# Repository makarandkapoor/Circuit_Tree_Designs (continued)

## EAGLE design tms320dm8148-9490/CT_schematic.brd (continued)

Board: 2 copper layers, 379 parts (0 on the bottom side), 196 nets, no tracks yet.

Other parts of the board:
J1: PJ-037B; PJ-037B_PACKAGE
U1: tms320dm8148SCYE2; BFBGA-684
U2: MD-40S
U3: AT25320B-SSHL-T; SOIC-8
U4: DP83867CSRGZT; VFQFPN48
U5: 7499511611A
U6: LAN8710AI-EZK; QFN-32
U7: 7498011122R
U8: 24AA1025T-I/SN; SOIC-8
U9: WM8731CLSEFL; QFN-28
U10, U11: SJ-43515TS-SMT-TR
U12, U13: ABLS-20.000MHZ-B4-T
U14: ABLS-25.000MHZ-B2F-T
U15: ASFL1-12.288MHZ-EC-T; ASFL1
U16: tps54525PWP; HTSSOP14
U17, U23: LP2951ACSDX/NOPB; WSON-8
U18, U19, U20: LTC3601EUD#PBF; QFN-16_EP
U21, U22: LP3878SDX-ADJ/NOPB; WSON-8
U24: LTC2928CUHF#PBF; QFN-38_UHF
U25, U26, U27, U28: IRF8306MTRPbF; IRF8306MTRPBF
U29: 4-1437565-2; SW_4-1437565-2
U30: Q65110A2395; LGM67K-G1J2-24-Z
U31, U32, U33: nc7sz125m5x; NC7SZ125M5X

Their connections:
CLK_CRYSTAL_U1_AH2: U1.AH2, U12.1; also elsewhere on the board
CLK_CRYSTAL_U1_AH3: U1.AH3, U12.2; also elsewhere on the board
CLK_CRYSTAL_U1_R1: U1.R1, U13.1; also elsewhere on the board
CLK_CRYSTAL_U1_T1: U1.T1, U13.2; also elsewhere on the board
CLK_CRYSTAL_U4_14: U4.14, U14.2; also elsewhere on the board
CLK_CRYSTAL_U4_15: U4.15, U14.1; also elsewhere on the board
CLK_U9_1: U9.1, U15.3
NET_U1_AA15: U1.AA15, U1.AA17, U1.AB14, U1.AB16, U1.M8, U1.N7, U1.P8, U1.T7, U1.U21, U1.U22, U1.V20, U1.Y11, U1.Y16
NET_U1_AA27: U1.AA27; also elsewhere on the board
NET_U1_AA28: U1.AA28; also elsewhere on the board
NET_U1_AB6: U1.AB6, U8.5; also elsewhere on the board
NET_U1_AB27: U1.AB27; also elsewhere on the board
NET_U1_AB28: U1.AB28; also elsewhere on the board
NET_U1_AC4: U1.AC4, U8.6; also elsewhere on the board
NET_U1_AG22: U1.AG22; also elsewhere on the board
NET_U1_AG23: U1.AG23; also elsewhere on the board
NET_U1_AH23: U1.AH23; also elsewhere on the board
NET_U1_B1: U1.B1; also elsewhere on the board
NET_U1_B27: U1.B27; also elsewhere on the board
NET_U1_G14: U1.G14; also elsewhere on the board
NET_U1_G15: U1.G15; also elsewhere on the board
NET_U1_H28: U1.H28, U4.16, U6.17; also elsewhere on the board
NET_U1_J5: U1.J5, U33.4; also elsewhere on the board
NET_U1_K12: U1.K9, U1.K12, U1.K18, U1.L15, U1.L17, U1.L19, U1.M16, U1.M18, U1.N17, U1.N19, U1.P12, U1.P14, U1.P16, U1.R15, U1.R17, U1.R19, U1.T12, U1.U11, U1.U13, U1.U17, U1.U19, U1.W11
NET_U1_L18: U1.L18; also elsewhere on the board
NET_U1_M11: U1.M11; also elsewhere on the board
NET_U1_N10: U1.N10; also elsewhere on the board
NET_U1_N11: U1.N11; also elsewhere on the board
NET_U1_P10: U1.P10; also elsewhere on the board
NET_U1_P18: U1.P18; also elsewhere on the board
NET_U1_P24: U1.P24, U4.17, U6.16; also elsewhere on the board
NET_U1_R11: U1.R11; also elsewhere on the board
NET_U1_T10: U1.T10; also elsewhere on the board
NET_U1_T11: U1.T11; also elsewhere on the board
NET_U1_U10: U1.U9, U1.U10
NET_U1_U23: U1.U23; also elsewhere on the board
NET_U1_U24: U1.U24; also elsewhere on the board
NET_U1_U25: U1.U25; also elsewhere on the board
NET_U1_U26: U1.U26; also elsewhere on the board
NET_U1_V14: U1.V14; also elsewhere on the board
NET_U1_V24: U1.V24; also elsewhere on the board
NET_U1_V25: U1.V25; also elsewhere on the board
NET_U1_V26: U1.V26; also elsewhere on the board
NET_U1_V27: U1.V27; also elsewhere on the board
NET_U1_W10: U1.W9, U1.W10
NET_U1_W14: U1.W14; also elsewhere on the board
NET_U1_W19: U1.W19, U1.W20
NET_U1_W27: U1.W27; also elsewhere on the board
NET_U1_Y25: U1.Y25; also elsewhere on the board
NET_U1_Y26: U1.Y26; also elsewhere on the board
NET_U1_Y27: U1.Y27; also elsewhere on the board
NET_U1_Y28: U1.Y28; also elsewhere on the board
NET_U2_3: U1.AH24, U2.3; also elsewhere on the board
NET_U2_4: U1.AH22, U2.4; also elsewhere on the board
NET_U3_3: U3.3; also elsewhere on the board
NET_U3_7: U3.7; also elsewhere on the board
NET_U4_12: U4.12; also elsewhere on the board
NET_U4_18: U4.18; also elsewhere on the board
NET_U4_20: U4.20; also elsewhere on the board
NET_U4_40: U4.40; also elsewhere on the board
NET_U4_43: U4.43, U31.4; also elsewhere on the board
NET_U4_44: U4.44; also elsewhere on the board
NET_U4_45: U4.45; also elsewhere on the board
NET_U4_46: U4.46; also elsewhere on the board
NET_U5_2: U4.8, U5.2
NET_U5_3: U4.7, U5.3
NET_U5_4: U4.4, U5.4
NET_U5_5: U4.5, U5.5
NET_U5_6: U5.1, U5.6, U5.7, U5.12; also elsewhere on the board
NET_U5_8: U4.10, U5.8
NET_U5_9: U4.11, U5.9
NET_U5_10: U4.2, U5.10
NET_U5_11: U4.1, U5.11
NET_U5_18: U5.18; also elsewhere on the board
NET_U5_19: U5.19; also elsewhere on the board
NET_U6_1: U6.1, U6.27; also elsewhere on the board
NET_U6_6: U6.6; also elsewhere on the board
NET_U6_7: U6.7; also elsewhere on the board
NET_U6_8: U6.8; also elsewhere on the board
NET_U6_9: U6.9; also elsewhere on the board
NET_U6_18: U6.18; also elsewhere on the board
NET_U6_19: U6.19, U32.4; also elsewhere on the board
NET_U6_32: U6.32; also elsewhere on the board
NET_U7_1: U6.29, U7.1; also elsewhere on the board
NET_U7_3: U6.28, U7.3; also elsewhere on the board
NET_U7_4: U6.31, U7.4; also elsewhere on the board
NET_U7_5: U7.2, U7.5; also elsewhere on the board
NET_U7_6: U6.30, U7.6; also elsewhere on the board
NET_U7_8: U7.8; also elsewhere on the board
NET_U7_9: U7.9; also elsewhere on the board
NET_U7_11: U6.2, U7.11
NET_U7_12: U7.12; also elsewhere on the board
NET_U7_13: U7.13, U7.14; also elsewhere on the board
NET_U8_1: U8.1; also elsewhere on the board
NET_U8_2: U8.2; also elsewhere on the board
NET_U8_3: U8.3; also elsewhere on the board
NET_U9_20: U9.20; also elsewhere on the board
NET_U10_2: U10.2; also elsewhere on the board
NET_U10_5: U10.5; also elsewhere on the board
NET_U11_5: U11.5; also elsewhere on the board
NET_U16_2: U16.2; also elsewhere on the board
NET_U16_3: U16.3; also elsewhere on the board
NET_U16_4: U16.4; also elsewhere on the board
NET_U16_10: U16.10, U16.11; also elsewhere on the board
NET_U16_12: U16.12; also elsewhere on the board
NET_U17_5: U17.5; also elsewhere on the board
NET_U17_7: U17.7; also elsewhere on the board
NET_U18_3: U18.3, U18.4; also elsewhere on the board
NET_U18_6: U18.6; also elsewhere on the board
NET_U18_7: U18.7, U18.12; also elsewhere on the board
NET_U18_10: U18.10; also elsewhere on the board
NET_U18_11: U18.11; also elsewhere on the board
NET_U19_3: U19.3, U19.4; also elsewhere on the board
NET_U19_6: U19.6; also elsewhere on the board
NET_U19_7: U19.7, U19.12; also elsewhere on the board
NET_U19_10: U19.10; also elsewhere on the board
NET_U19_11: U19.11; also elsewhere on the board
NET_U20_3: U20.3, U20.4; also elsewhere on the board
NET_U20_6: U20.6; also elsewhere on the board
NET_U20_7: U20.7, U20.12; also elsewhere on the board
NET_U20_10: U20.10; also elsewhere on the board
NET_U20_11: U20.11; also elsewhere on the board
NET_U21_1: U21.1; also elsewhere on the board
NET_U21_6: U21.6; also elsewhere on the board
NET_U21_8: U21.8; also elsewhere on the board
NET_U22_1: U22.1; also elsewhere on the board
NET_U22_6: U22.6; also elsewhere on the board
NET_U22_8: U22.8; also elsewhere on the board
NET_U23_5: U23.5; also elsewhere on the board
NET_U23_7: U23.7; also elsewhere on the board
NET_U24_3: U24.3; also elsewhere on the board
NET_U24_6: U24.6; also elsewhere on the board
NET_U24_7: U24.7; also elsewhere on the board
NET_U24_8: U24.8; also elsewhere on the board
NET_U24_9: U24.9; also elsewhere on the board
NET_U24_16: U24.16; also elsewhere on the board
NET_U24_18: U24.18; also elsewhere on the board
NET_U24_19: U24.19, U24.20; also elsewhere on the board
NET_U24_21: U24.21, U31.2, U32.2, U33.2; also elsewhere on the board
NET_U24_22: U24.11, U24.22; also elsewhere on the board
NET_U24_26: U24.26; also elsewhere on the board
NET_U24_27: U24.27; also elsewhere on the board
NET_U24_28: U24.28; also elsewhere on the board
NET_U24_30: U24.30; also elsewhere on the board
NET_U24_32: U24.32; also elsewhere on the board
NET_U24_38: U24.38; also elsewhere on the board
NET_U25_3: U24.2, U25.3
NET_U26_3: U24.37, U26.3
NET_U27_3: U24.31, U27.3
NET_U28_3: U24.29, U28.3
NET_U29_1: U29.1, U29.2
NET_U29_3: U29.3, U29.4
PROC_EMAC0_RGRXC: U1.L24, U4.32
PROC_EMAC0_RGRXCTL: U1.L23, U4.38; also elsewhere on the board
PROC_EMAC0_RGRXD0: U1.P23, U4.33; also elsewhere on the board
PROC_EMAC0_RGRXD1: U1.R23, U4.34; also elsewhere on the board
PROC_EMAC0_RGRXD2: U1.R25, U4.35
PROC_EMAC0_RGRXD3: U1.T23, U4.36
PROC_EMAC0_RGTXC: U1.H27, U4.29
PROC_EMAC0_RGTXCTL: U1.J26, U4.37
PROC_EMAC0_RGTXD0: U1.G28, U4.28
PROC_EMAC0_RGTXD1: U1.G27, U4.27
PROC_EMAC0_RGTXD2: U1.F28, U4.26
PROC_EMAC0_RGTXD3: U1.H26, U4.25
PROC_EMAC1_RMCRSDV: U1.AC17, U6.15; also elsewhere on the board
PROC_EMAC1_RMRXD0: U1.H22, U6.11; also elsewhere on the board
PROC_EMAC1_RMRXD1: U1.AF20, U6.10; also elsewhere on the board
PROC_EMAC1_RMRXER: U1.AB21, U6.13; also elsewhere on the board
PROC_EMAC1_RMTXD0: U1.AE18, U6.22
PROC_EMAC1_RMTXD1: U1.AC21, U6.23
PROC_EMAC1_RMTXEN: U1.AC16, U6.21
PROC_MCA0_ACLKX: U1.R4, U9.7
PROC_MCA0_AFSX: U1.L3, U9.9, U9.11
PROC_MCA0_AXR7: U1.L2, U9.10
PROC_MCA0_AXR8: U1.L1, U9.8
PROC_SPI0_D0: U1.AE3, U3.5
PROC_SPI0_D1: U1.AF3, U3.2
PROC_SPI0_SCLK: U1.AC7, U3.6
PROC_SPI0_SCS0: U1.AD6, U3.1; also elsewhere on the board
VCC_13V3: J1.1, U24.23, U25.1, U25.2, U25.6, U25.7, U26.1, U26.2, U26.6, U26.7, U27.1, U27.2, U27.6, U27.7, U28.1, U28.2, U28.6, U28.7; also elsewhere on the board
VCC_S1_13V3: U16.7, U16.13, U16.14, U17.8, U25.4, U25.5; also elsewhere on the board
VCC_S2_13V3: U18.15, U18.16, U26.4, U26.5; also elsewhere on the board
VCC_S3_13V3: U19.15, U19.16, U20.15, U20.16, U21.4, U22.4, U27.4, U27.5; also elsewhere on the board
VCC_S4_13V3: U23.8, U28.4, U28.5; also elsewhere on the board
VCC_TIER1_1V35: U1.K9, U1.K10, U1.L9, U1.L10, U1.L11, U1.L12, U1.L14, U1.L15, U1.M10, U1.M12, U1.M13, U1.M14, U1.N9, U1.N13, U1.N14, U1.T14, U1.T15, U1.T16, U1.U15, U1.U16, U1.V15, U1.V16, U16.1; also elsewhere on the board
VCC_TIER1_3V3: U15.4, U17.1, U31.5, U32.5, U33.5; also elsewhere on the board
VCC_TIER3_2V5: U4.3, U4.9, U21.5; also elsewhere on the board
VCC_TIER3_3V3: U22.5; also elsewhere on the board
VCC_TIER4_3V3: U1.AA13, U23.1; also elsewhere on the board

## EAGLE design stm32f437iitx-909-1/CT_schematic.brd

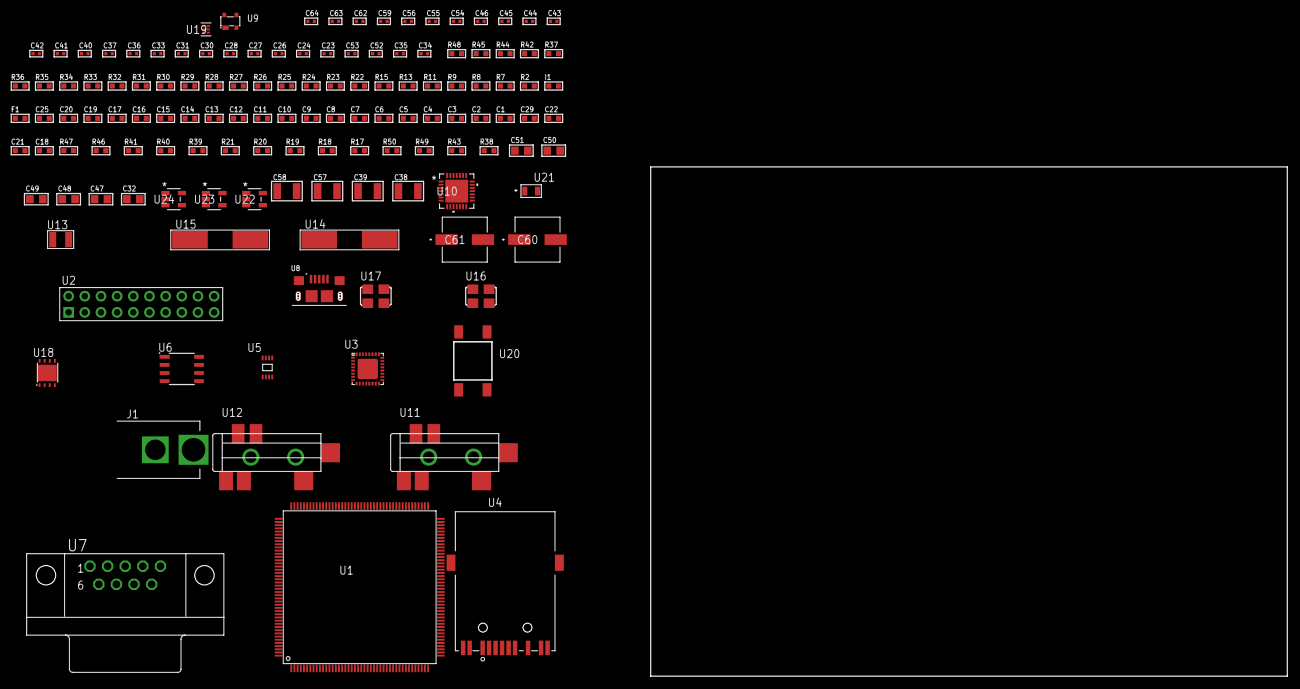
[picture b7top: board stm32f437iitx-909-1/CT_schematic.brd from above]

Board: 2 copper layers, 132 parts (0 on the bottom side), 80 nets, no tracks yet.

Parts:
C1, C20, C25: 1e-06; C0603
C2, C3, C4, C5, C6, C7, C8, C9, C10, C11, C12, C13, C14, C15, C16, C17: 1e-07; C0603
C18: 4.7e-06; C0603
C19: 1e-08; C0603
C21, C22, C29: 2.2e-06; C0603
C23, C24: 1e-11; C0402
C26, C27, C28, C30, C31, C33, C37, C42, C43, C44, C45, C46, C59: 1e-07; C0402
C32, C47, C48, C49, C50, C51: 1e-05; C0805
C34, C35, C52, C53: 2.2e-11; C0402
C36, C54, C55, C56, C62, C63, C64: 1e-08; C0402
C38, C39: 2.2e-05; C1210
C40, C41: 1e-09; C0402
C57, C58: 1e-05; C1210
C60, C61: 0.0001; EXV-9H
F1: 240.0; L0603
I1: 97.0; R0603
J1: PJ-037B; PJ-037B_PACKAGE
R2, R31, R33, R34, R35, R45: 1000.0; R0603
R7, R8, R27, R28, R29, R30, R32, R36: 4700.0; R0603
R9, R11, R13, R15: 2200.0; R0603
R17, R18, R19, R20, R21, R46, R47: 10000.0; R0603
R22, R23: 0.1; R0603
R24: 200.0; R0603
R25: 220.0; R0603
R26: 6490.0; R0603
R37: 120.0; R0603
R38: 470000.0; R0603
R39, R40, R41: 47000.0; R0603
R42: 680.0; R0603
R43: 100000.0; R0603
R44: 2231.0; R0603
R48: 9100.0; R0603
R49: 680000.0; R0603
R50: 120000.0; R0603
U1: STM32F437IIT6; LQFP176
U2: TST-110-05-T-D-RA
U3: KSZ8081RNBIA-TR; QFN-32
U4: 7498011122R
U5: 24AA08T-I/MNY; TDFN-8/6MM
U6: SN65HVD230D; SOIC-8
U7: 182-009-113R531; 182-009-MALE
U8: 10118193-0001LF; FCI_10118193-0001LF
U9: prtr5v0u2ax; SOT143B
U10: WM8731CLSEFL; QFN-28
U11, U12: SJ-43515TS-SMT-TR
U13: ABS07-32.768KHZ-7-T
U14: ABLS-25.000MHZ-B2F-T
U15: ABLS-12.288MHZ-B4-T
U16: ASFL1-25MHZ-NCS; ASFL1
U17: ASFL1-50MHZ-NCS; ASFL1
U18: LP3878SDX-ADJ/NOPB; WSON-8
U19: TPS3895ADRYR; SON-6
U20: 4-1437565-2; SW_4-1437565-2
U21: Q65110A2395; LGM67K-G1J2-24-Z
U22, U23, U24: nc7sz125m5x; NC7SZ125M5X

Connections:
CLK_CRYSTAL_U1_9: C23.1, U1.9, U13.1
CLK_CRYSTAL_U1_10: C24.1, U1.10, U13.2
CLK_CRYSTAL_U3_8: C34.1, U3.8, U14.2
CLK_CRYSTAL_U3_9: C35.1, U3.9, U14.1
CLK_CRYSTAL_U10_1: C52.1, U10.1, U15.1
CLK_CRYSTAL_U10_2: C53.1, U10.2, U15.2
CLK_U1_29: U1.29, U16.3
CLK_U1_41: U1.41, U17.3
GND: C1.2, C2.2, C3.2, C4.2, C5.2, C6.2, C7.2, C8.2, C9.2, C10.2, C11.2, C12.2, C13.2, C14.2, C15.2, C16.2, C17.2, C18.2, C19.2, C20.2, C21.2, C22.2, C23.2, C24.2, C25.2, C26.2, C27.2, C28.2, C29.2, C30.2, C31.2, C32.2, C33.2, C34.2, C35.2, C36.2, C37.2, C41.2, C42.2, C43.2, C44.2, C45.2, C46.2, C47.2, C48.2, C49.2, C50.2, C51.2, C52.2, C53.2, C54.2, C55.2, C56.2, C57.2, C58.2, C59.2, C60.2, C61.2, C62.2, C63.2, C64.2, J1.2, R2.2, R20.2, R22.2, R23.2, R26.2, R28.2, R31.2, R33.2, R34.2, R35.2, R38.2, R39.2, R40.2, R41.2, R45.2, R48.2, R50.2, U1.14, U1.22, U1.37, U1.61, U1.71, U1.90, U1.102, U1.113, U1.122, U1.126, U1.135, U1.148, U1.158, U2.4, U2.6, U2.8, U2.10, U2.12, U2.14, U2.16, U2.18, U2.20, U3.1, U3.EXP, U4.1, U4.10, U5.4, U5.7, U6.2, U7.5, U8.5, U8.6, U8.7, U8.8, U8.9, U9.1, U10.4, U10.15, U10.19, U10.25, U10.26, U10.29, U11.1, U12.1, U16.2, U17.2, U18.3, U18.PAD, U19.2, U21.C, U22.2, U22.3, U23.1, U23.3, U24.1, U24.3
NET_U1_31: R8.1, U1.31, U24.4
NET_U1_33: R13.1, U1.33, U3.12
NET_U1_39: C19.1, C20.1, F1.1, U1.38, U1.39
NET_U1_42: R15.1, U1.42, U3.11
NET_U1_48: R20.1, U1.48
NET_U1_58: R19.1, U1.58
NET_U1_81: C21.1, U1.81
NET_U1_125: C22.1, U1.125
NET_U1_164: R9.1, U1.164, U5.6
NET_U1_165: R11.1, U1.165, U5.5
NET_U1_166: R18.1, U1.166
NET_U1_171: R17.1, U1.171
NET_U1_176: U20.3, U20.4
NET_U3_2: C29.1, C30.1, U3.2
NET_U3_3: C31.1, I1.1, U3.3
NET_U3_10: R26.1, U3.10
NET_U3_13: R29.1, U3.13
NET_U3_14: R30.1, U3.14
NET_U3_19: R28.1, U3.19
NET_U3_20: R34.1, U3.20
NET_U3_21: R27.1, U3.21
NET_U3_28: R32.1, U3.28
NET_U3_29: R33.1, U3.29
NET_U3_31: R35.1, U3.31
NET_U3_32: R7.1, U3.32, U23.4
NET_U4_1: U3.7, U4.1
NET_U4_2: C27.1, U4.2
NET_U4_3: U3.6, U4.3
NET_U4_4: U3.5, U4.4
NET_U4_5: C28.1, U4.5
NET_U4_6: U3.4, U4.6
NET_U4_8: R23.1, U4.8
NET_U4_9: R24.1, U4.9
NET_U4_12: R25.1, U4.12
NET_U4_13: R22.1, U4.13, U4.14
NET_U6_6: R37.2, U6.6
NET_U6_8: R38.1, U6.8
NET_U7_2: R37.2, U6.6, U7.2
NET_U7_3: R37.1, U6.7, U7.3
NET_U10_20: C46.1, C51.1, U10.20
NET_U11_2: C39.1, R40.1, U11.2
NET_U11_5: C38.1, R39.1, U11.5
NET_U12_5: C40.1, C41.1, R41.1, R42.1, U12.5
NET_U18_1: C56.1, U18.1
NET_U18_6: R44.2, R45.1, U18.6
NET_U18_8: R43.1, U18.8
NET_U19_1: R47.1, R48.1, U19.1
NET_U19_3: R49.2, R50.1, U19.3
NET_U19_4: R46.1, U19.4, U22.4, U23.2, U24.2
NET_U20_1: R2.1, U20.1, U20.2
PROC_CAN1_RX: U1.11, U6.4
PROC_CAN1_TX: U1.128, U6.1
PROC_ETH_CRS_DV: U1.53, U3.18
PROC_ETH_RXD0: R36.1, U1.54, U3.16
PROC_ETH_RXD1: R31.1, U1.55, U3.15
PROC_ETH_TXD0: U1.92, U3.24
PROC_ETH_TXD1: U1.93, U3.25
PROC_ETH_TX_EN: U1.80, U3.23
PROC_I2S2_CK: U1.79, U10.7
PROC_I2S2_EXT_SD: U1.34, U10.10
PROC_I2S2_SD: U1.35, U10.8
PROC_I2S2_WS: U1.131, U10.9, U10.11
PROC_SYS_JTCK_SWCLK: U1.137, U2.9
PROC_SYS_JTDO_SWO: U1.161, U2.13
PROC_SYS_JTMS_SWDIO: U1.124, U2.7
PROC_USB_OTG_FS_DM: U1.122, U8.2, U9.3
PROC_USB_OTG_FS_DP: U1.123, U8.3, U9.2
PROC_USB_OTG_FS_VBUS: C25.1, U1.120, U8.1, U9.4
RST_OUT_U2_SRESET_B: R21.1, U2.15, U22.1
VCC_S1_12V1: C57.1, C60.1, C61.1, J1.1, R43.2, U18.4
VCC_TIER1_3V3: C1.1, C2.1, C3.1, C4.1, C5.1, C6.1, C7.1, C8.1, C9.1, C10.1, C11.1, C12.1, C13.1, C14.1, C15.1, C16.1, C17.1, C18.1, C26.1, C32.1, C33.1, C36.1, C37.1, C42.1, C43.1, C44.1, C45.1, C47.1, C48.1, C49.1, C50.1, C54.1, C55.1, C58.1, C59.1, C62.1, C63.1, C64.1, F1.2, I1.2, R7.2, R8.2, R9.2, R11.2, R13.2, R15.2, R17.2, R18.2, R19.2, R21.2, R27.2, R29.2, R30.2, R32.2, R36.2, R44.1, R46.2, R47.2, R49.1, U1.6, U1.15, U1.23, U1.36, U1.49, U1.62, U1.72, U1.82, U1.91, U1.103, U1.114, U1.127, U1.136, U1.149, U1.159, U1.172, U2.1, U3.17, U5.8, U6.3, U10.3, U10.5, U10.12, U10.18, U16.4, U17.4, U18.5, U19.6, U22.5, U23.5, U24.5

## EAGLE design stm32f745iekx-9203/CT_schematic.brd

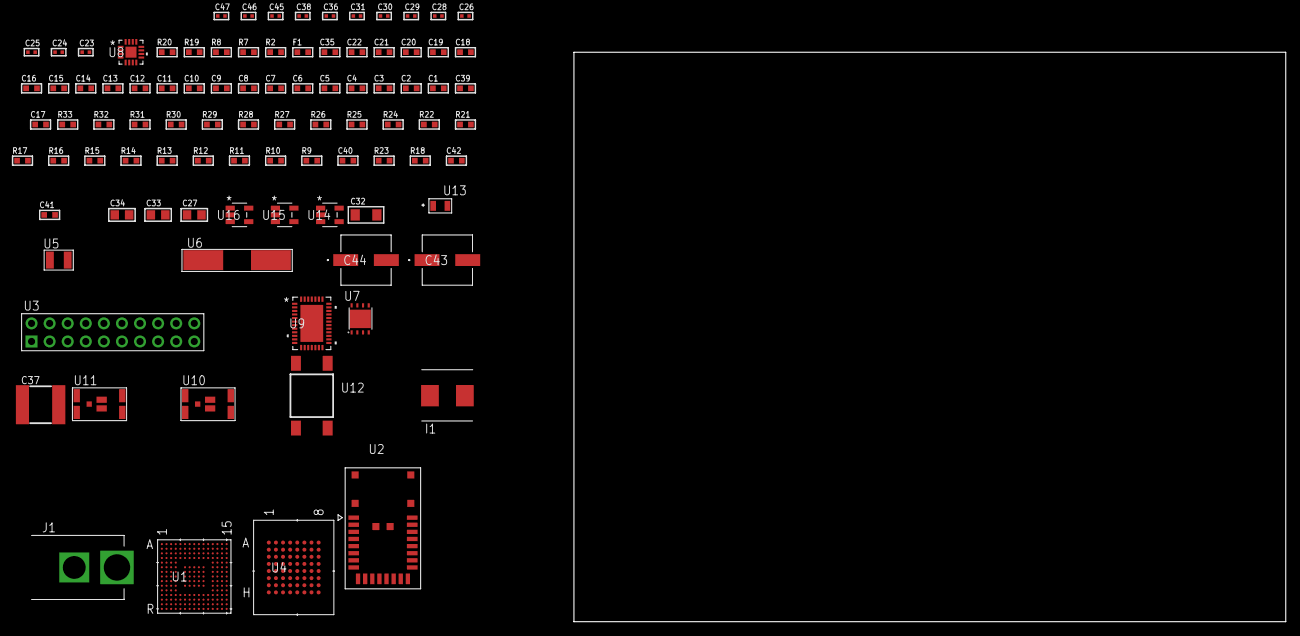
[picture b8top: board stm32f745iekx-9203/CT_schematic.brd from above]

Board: 2 copper layers, 100.0 x 80.0 mm, 94 parts (0 on the bottom side), 91 nets, no tracks yet.

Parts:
C1, C19, C35: 1e-06; C0603
C2, C3, C4, C5, C6, C7, C8, C9, C10, C11, C12, C13, C14, C15, C16, C20, C21, C22: 1e-07; C0603
C17: 4.7e-06; C0603
C18: 1e-08; C0603
C23, C24, C25, C26: 1e-11; C0402
C27, C33, C34: 1e-05; C0805
C28, C36, C38: 1e-07; C0402
C29, C30, C31, C45, C46, C47: 1e-08; C0402
C32: 1e-05; C1206
C37: 6.8e-05; 2220
C39: 2.2e-06; C0603
C40: 2.45e-08; R0603
C41: 2.8258362168397e-09; R0603
C42: 7.105e-09; R0603
C43, C44: 0.0001; EXV-9H
F1: 240.0; L0603
I1: 3.3e-06; WE-HCI_7030/7040/7050
J1: PJ-037B; PJ-037B_PACKAGE
R2, R20: 1000.0; R0603
R7, R8: 4700.0; R0603
R9, R10, R11, R12, R13, R14, R15, R16, R17, R24, R26, R27, R30, R31, R32: 10000.0; R0603
R18: 100000.0; R0603
R19: 200.0; R0603
R21: 20000.0; R0603
R22: 91000.0; R0603
R23: 300000.0; R0603
R25: 75000.0; R0603
R28, R29: 95300.0; R0603
R33: 49900.0; R0603
U1: STM32F745IEK7; UFBGA176_25
U2: A2500R24A00GM
U3: TST-110-05-T-D-RA
U4: mt28ew512aba1HPC-0AAT; LBGA-64
U5: ABS07-32.768KHZ-7-T
U6: ABLS-25.000MHZ-B2F-T
U7: LP3878SDX-ADJ/NOPB; WSON-8
U8: LTC3601EUD#PBF; QFN-16_EP
U9: LTC2928CUHF#PBF; QFN-38_UHF
U10, U11: IRF8306MTRPbF; IRF8306MTRPBF
U12: 4-1437565-2; SW_4-1437565-2
U13: Q65110A2395; LGM67K-G1J2-24-Z
U14, U15, U16: nc7sz125m5x; NC7SZ125M5X

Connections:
CLK_CRYSTAL_U1_E1: C23.1, U1.E1, U5.1
CLK_CRYSTAL_U1_F1: C24.1, U1.F1, U5.2
CLK_CRYSTAL_U1_G1: C25.1, U1.G1, U6.1
CLK_CRYSTAL_U1_H1: C26.1, U1.H1, U6.2
GND: C1.2, C2.2, C3.2, C4.2, C5.2, C6.2, C7.2, C8.2, C9.2, C10.2, C11.2, C12.2, C13.2, C14.2, C15.2, C16.2, C17.2, C18.2, C19.2, C20.2, C21.2, C22.2, C23.2, C24.2, C25.2, C26.2, C27.2, C28.2, C29.2, C30.2, C31.2, C32.2, C33.2, C34.2, C35.2, C37.1, C37.2, C38.2, C39.2, C40.2, C41.2, C42.2, C43.2, C44.2, C45.2, C46.2, C47.2, J1.2, R2.2, R9.2, R20.2, R21.2, R23.2, R25.2, R28.2, R29.2, R30.2, R31.2, R32.2, U1.D5, U1.D7, U1.D8, U1.D9, U1.F2, U1.F6, U1.F7, U1.F8, U1.F9, U1.F10, U1.F12, U1.G2, U1.G6, U1.G7, U1.G8, U1.G9, U1.G10, U1.G12, U1.H6, U1.H7, U1.H8, U1.H9, U1.H10, U1.H12, U1.J6, U1.J7, U1.J8, U1.J9, U1.J10, U1.K6, U1.K7, U1.K8, U1.K9, U1.K10, U1.M1, U1.M8, U1.M9, U1.N1, U2.8, U2.17, U3.4, U3.6, U3.8, U3.10, U3.12, U3.14, U3.16, U3.18, U3.20, U4.E8, U4.H2, U4.H7, U7.3, U7.PAD, U8.1, U8.9, U8.17, U9.8, U9.9, U9.10, U9.12, U9.13, U9.24, U9.25, U9.30, U9.32, U9.39, U13.C, U14.2, U14.3, U15.1, U15.3, U16.1, U16.3
NET_U1_C6: R10.1, U1.C6
NET_U1_D6: R9.1, U1.D6
NET_U1_F13: C22.1, U1.F13
NET_U1_J1: R8.1, U1.J1, U16.4
NET_U1_L4: R11.1, U1.L4
NET_U1_R1: C18.1, C19.1, F1.1, U1.P1, U1.R1
NET_U1_R15: U12.3, U12.4
NET_U4_B4: R16.1, U4.B4
NET_U4_B5: R7.1, U4.B5, U15.4
NET_U7_1: C31.1, U7.1
NET_U7_6: R19.2, R20.1, U7.6
NET_U7_8: R18.1, U7.8
NET_U8_3: C36.2, I1.1, U8.3, U8.4
NET_U8_6: C36.1, U8.6
NET_U8_7: C35.1, U8.7, U8.12
NET_U8_10: R23.1, U8.10
NET_U8_11: R21.1, R22.1, U8.11
NET_U8_ATNET_3: I1.2, R22.2
NET_U9_3: R31.1, U9.3
NET_U9_6: R28.1, U9.6
NET_U9_7: R29.1, U9.7
NET_U9_16: R30.1, R33.1, U9.16
NET_U9_18: R27.1, U9.18
NET_U9_19: R26.1, U9.19, U9.20
NET_U9_21: R24.1, R25.1, U9.21, U14.4, U15.2, U16.2
NET_U9_26: C41.1, U9.26
NET_U9_27: C40.1, U9.27
NET_U9_28: C42.1, U9.28
NET_U9_38: R32.1, U9.38
NET_U10_3: U9.2, U10.3
NET_U11_3: U9.37, U11.3
NET_U12_1: R2.1, U12.1, U12.2
PROC_FMC_A0: U1.E2, U4.E2
PROC_FMC_A1: U1.H3, U4.D2
PROC_FMC_A2: U1.H2, U4.C2
PROC_FMC_A3: U1.J2, U4.A2
PROC_FMC_A4: U1.J3, U4.B2
PROC_FMC_A5: U1.K3, U4.D3
PROC_FMC_A6: U1.P6, U4.C3
PROC_FMC_A9: U1.P7, U4.A6
PROC_FMC_A10: U1.N7, U4.C6
PROC_FMC_A11: U1.M7, U4.D6
PROC_FMC_A12: U1.L15, U4.B7
PROC_FMC_A13: U1.K15, U4.A7
PROC_FMC_A14: U1.K14, U4.C7
PROC_FMC_A15: U1.K13, U4.D7
PROC_FMC_A16: U1.N14, U4.E7
PROC_FMC_A17: U1.N13, U4.B3
PROC_FMC_A18: U1.M15, U4.C4
PROC_FMC_A19: U1.A1, U4.D5
PROC_FMC_A20: U1.B1, U4.D4
PROC_FMC_A21: U1.B2, U4.C5
PROC_FMC_A22: U1.B3, U4.B8
PROC_FMC_A23: U1.A2, U4.C8
PROC_FMC_A24: U1.A8, U4.F8
PROC_FMC_D0: U1.M14, U4.E3
PROC_FMC_D1: U1.L14, U4.H3
PROC_FMC_D2: U1.B12, U4.E4
PROC_FMC_D3: U1.C12, U4.H4
PROC_FMC_D4: U1.R8, U4.H5
PROC_FMC_D5: U1.P8, U4.E5
PROC_FMC_D6: U1.P9, U4.H6
PROC_FMC_D7: U1.R9, U4.E6
PROC_FMC_D8: U1.P10, U4.F3
PROC_FMC_D9: U1.R10, U4.G3
PROC_FMC_D10: U1.N11, U4.F4
PROC_FMC_D11: U1.P11, U4.G4
PROC_FMC_D12: U1.R11, U4.F5
PROC_FMC_D13: U1.P15, U4.G6
PROC_FMC_D14: U1.P14, U4.F6
PROC_FMC_D15: U1.N15, U4.G7
PROC_FMC_NBL0: R17.1, U1.A4, U4.F7
PROC_FMC_NE2: R13.1, U1.C10, U4.F2
PROC_FMC_NOE: R14.1, U1.D10, U4.G2
PROC_FMC_NWAIT: U1.B11, U4.A4
PROC_FMC_NWE: R15.1, U1.C11, U4.A5
PROC_SPI1_MISO: U1.A9, U2.10
PROC_SPI1_MOSI: U1.A6, U2.11
PROC_SPI1_NSS: U1.A13, U2.12
PROC_SPI1_SCK: U1.P4, U2.9
RST_OUT_U3_SRESET_B: R12.1, U3.15, U14.1
VCC_6V7: C38.1, C39.1, C43.1, C44.1, J1.1, R24.2, R26.2, R27.2, R33.2, U9.11, U9.22, U10.1, U10.2, U10.6, U10.7, U11.1, U11.2, U11.6, U11.7
VCC_S1_6V7: C32.1, C34.1, R18.2, U7.4, U8.15, U8.16, U10.4, U10.5
VCC_S2_6V7: U11.4, U11.5
VCC_TIER1_1V2: C21.1, C33.1, R19.1, U1.M10, U7.5
VCC_TIER1_3V3: C1.1, C2.1, C3.1, C4.1, C5.1, C6.1, C7.1, C8.1, C9.1, C10.1, C11.1, C12.1, C13.1, C14.1, C15.1, C16.1, C17.1, C20.1, C27.1, C28.1, C29.1, C30.1, C37.2, C45.1, C46.1, C47.1, F1.2, I1.2, R7.2, R8.2, R10.2, R11.2, R12.2, R13.2, R14.2, R15.2, R16.2, R17.2, R22.2, U1.C1, U1.C5, U1.C7, U1.C8, U1.C9, U1.F3, U1.G3, U1.G13, U1.H13, U1.J12, U1.J13, U1.K4, U1.N8, U1.N9, U1.N10, U2.18, U3.1, U4.D8, U4.F1, U4.G5, U8.8, U14.5, U15.5, U16.5

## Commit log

2017-09-07 Readme.txt
2017-09-08 First set of files.
2017-09-08 Second set of files
2017-09-08 Next set of files
2017-09-08 Next set of files.
2017-09-08 Next set of Design files.
2017-09-08 Next set of design files
2017-09-09 Next set of designs
2017-09-10 Small drone Board design checkin
2017-09-12 Added readme.md file.
2017-09-28 Manually updated schematics and placement file
2017-10-10 Released Drone design board and schematic file.
2017-10-13 Added schematic pdf file.
2017-11-03 Create Readme.md for am3356 folder
2017-11-03 Edited readme.md file
2018-02-01 STM code to run the drone board.
    Contains ported drivers from stm library.
2018-09-21 Update readme.md
    Updated readme.md file
2018-09-21 Update readme.md
    Updated readme.md
2018-09-25 Added design files
